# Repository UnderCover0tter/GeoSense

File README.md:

# GeoSense
This repository is the hub for documentation and files created for the project dubbed "GeoSence". 

The goal of this project is to make a circuit to allow for more accurate measuring of a thermistor.
To do achieve this goal a instrumentation amplifier circuit has ben designed for the respective thermistor and operating range of the application.

A later goal is to write a program that will interpret the circuits output from an A to D to get and log the temperatures measured.

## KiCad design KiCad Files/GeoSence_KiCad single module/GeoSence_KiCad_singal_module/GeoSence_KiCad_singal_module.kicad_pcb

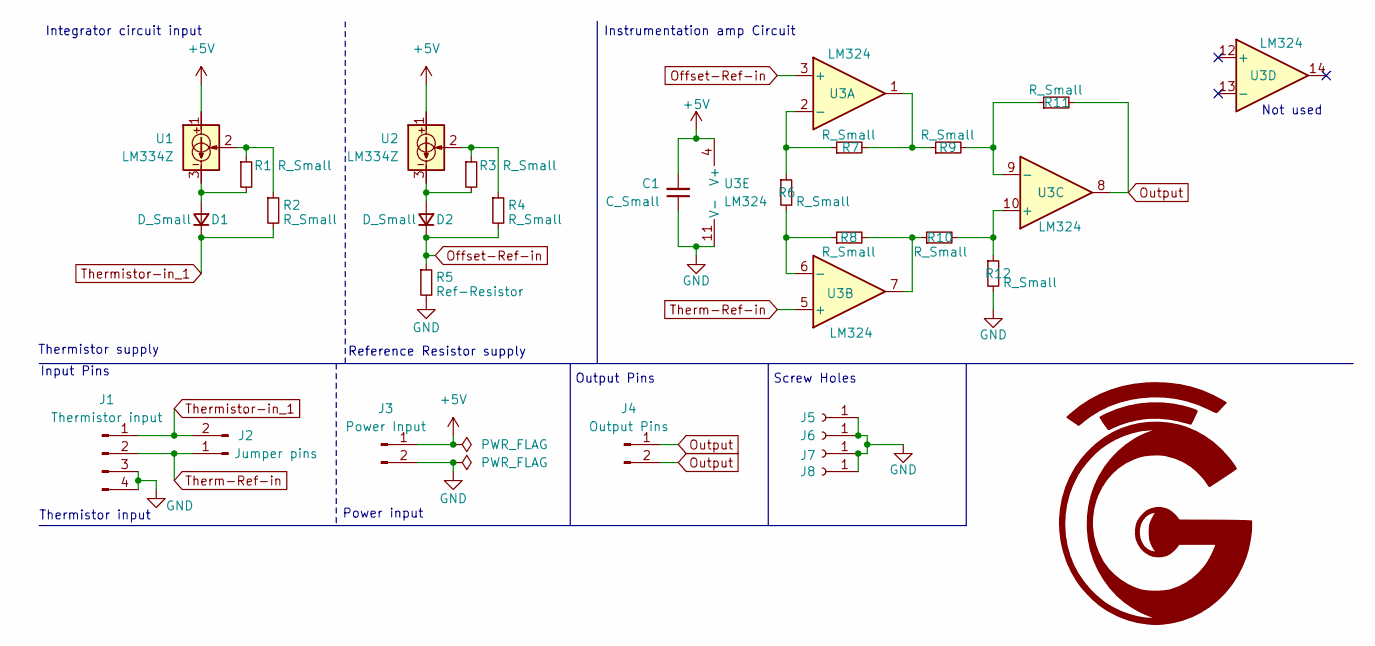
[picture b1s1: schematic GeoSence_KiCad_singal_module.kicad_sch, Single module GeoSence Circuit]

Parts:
C1: C_Small; C_0805_2012Metric
D1, D2: D_Small; D_DO-35_SOD27_P7.62mm_Horizontal
J1: Thermistor input; PinHeader_1x04_P2.54mm_Vertical
J2: Jumper pins; PinHeader_1x02_P2.54mm_Vertical
J3: Power Input; PinHeader_1x02_P2.54mm_Vertical
J4: Output Pins; PinHeader_1x02_P2.54mm_Vertical
J5, J6, J7, J8: Conn_01x01_Socket; MountingHole_3.2mm_M3_DIN965_Pad_TopBottom
R1, R2, R3, R4, R6, R7, R8, R9, R10, R11, R12: R_Small; R_Axial_DIN0204_L3.6mm_D1.6mm_P5.08mm_Horizontal
R5: Ref-Resistor; R_Axial_DIN0204_L3.6mm_D1.6mm_P5.08mm_Horizontal
U1, U2: LM334Z; TO-92_Inline
U3: LM324; TSSOP-14_4.4x5mm_P0.65mm

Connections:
+5V: C1.2, J3.1, U1.1, U2.1, U3.4 (V+)
GND: C1.1, J1.3, J1.4, J3.2, J5.1, J6.1, J7.1, J8.1, R5.2, R12.2, U3.11 (V-)
unnamed: D1.2 (A), R1.2, U1.3
unnamed: D2.2 (A), R3.2, U2.3
unnamed: R1.1, R2.1, U1.2
unnamed: R3.1, R4.1, U2.2
unnamed: R7.2, R9.1, U3.1
unnamed: R8.2, R10.1, U3.7
unnamed: R6.1, R7.1, U3.2 (-)
unnamed: R6.2, R8.1, U3.6 (-)
unnamed: R10.2, R12.1, U3.10 (+)
unnamed: R9.2, R11.1, U3.9 (-)
Offset-Ref-in: D2.1 (K), R4.2, R5.1, U3.3 (+)
Output: J4.1, J4.2, R11.2, U3.8
Therm-Ref-in: J1.2, J2.1, U3.5 (+)
Thermistor-in_1: D1.1 (K), J1.1, J2.2, R2.2

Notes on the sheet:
Reference Resistor supply
Thermistor supply
Thermistor input
Output Pins
Power input
Instrumentation amp Circuit
Not used
Screw Holes
Integrator circuit input
Input Pins

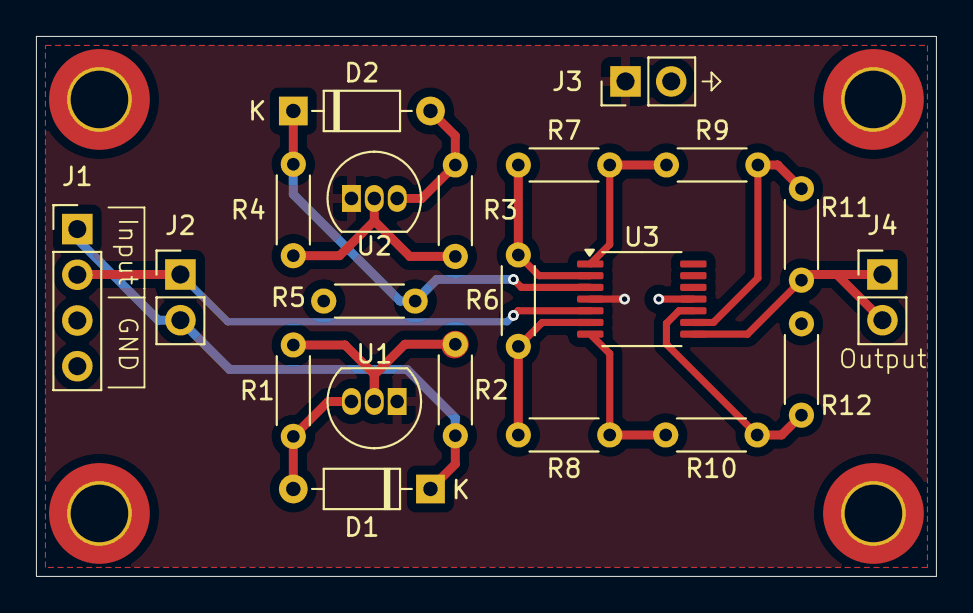
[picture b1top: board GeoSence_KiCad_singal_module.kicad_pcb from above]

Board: 2 copper layers, 50.0 x 30.0 mm, 26 parts (1 on the bottom side), 16 nets.

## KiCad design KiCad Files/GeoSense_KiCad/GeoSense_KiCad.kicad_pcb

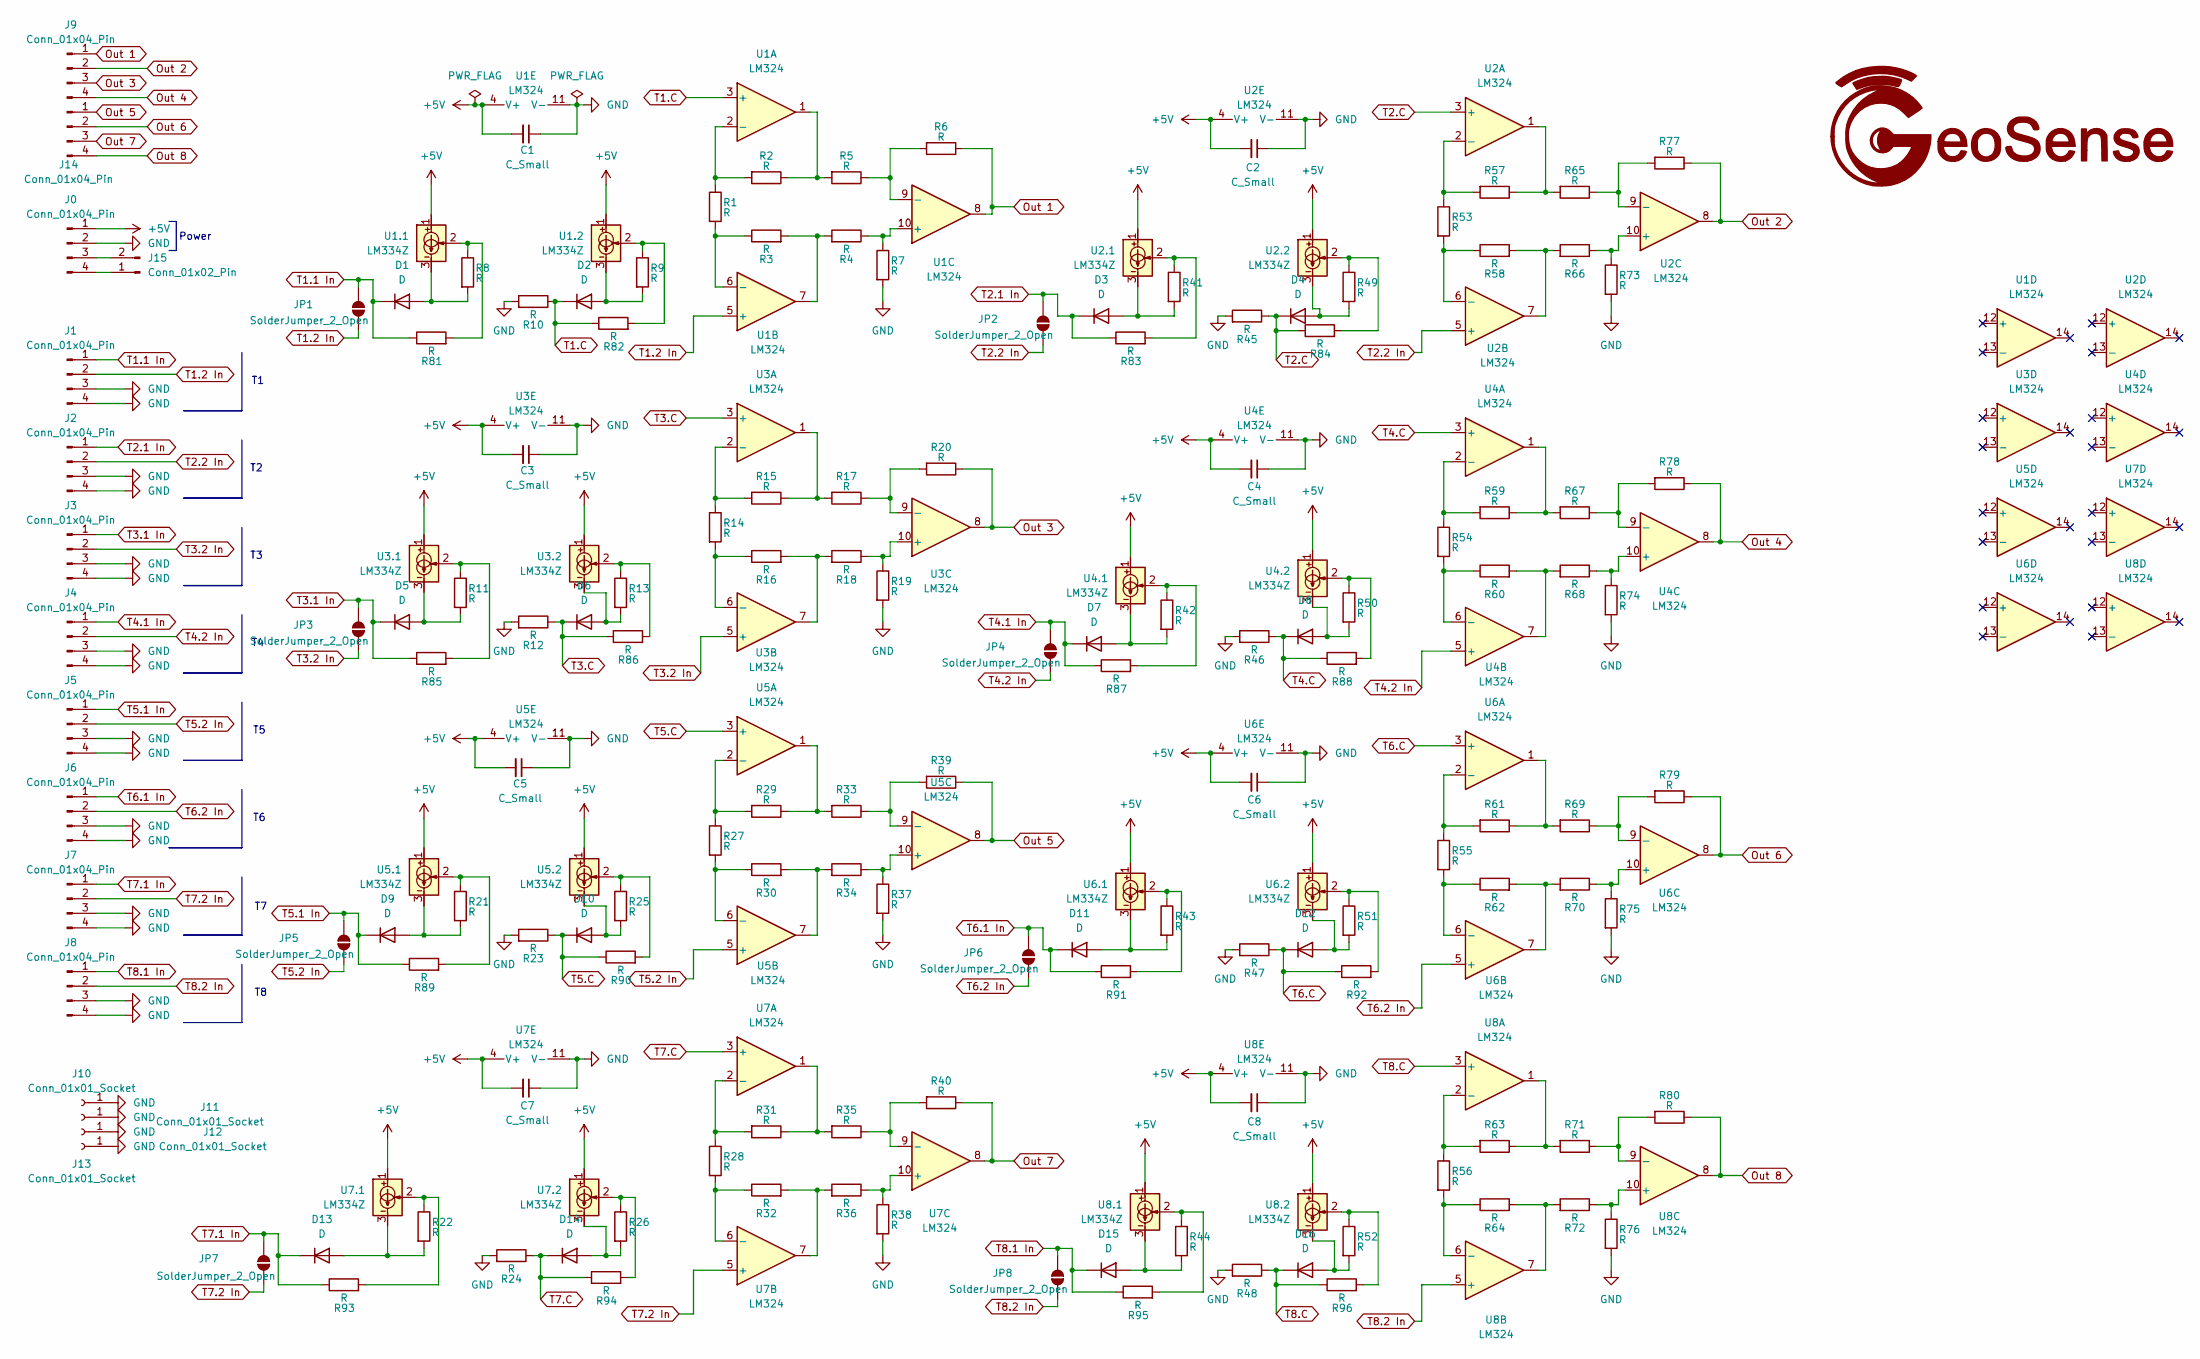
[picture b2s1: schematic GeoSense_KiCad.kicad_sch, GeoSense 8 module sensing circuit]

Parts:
C1, C2, C3, C4, C5, C6, C7, C8: C_Small; C_0603_1608Metric
D1, D2, D3, D4, D5, D6, D7, D8, D9, D10, D11, D12, D13, D14, D15, D16: D; D_DO-35_SOD27_P7.62mm_Horizontal
J0, J1, J2, J3, J4, J5, J6, J7, J8, J9, J14: Conn_01x04_Pin; PinHeader_1x04_P2.54mm_Vertical
J10, J11, J12, J13: Conn_01x01_Socket; MountingHole_3.2mm_M3_DIN965_Pad_TopBottom
J15: Conn_01x02_Pin; PinHeader_1x02_P2.54mm_Vertical
JP1, JP2, JP3, JP4, JP5, JP6, JP7, JP8: SolderJumper_2_Open; SolderJumper-2_P1.3mm_Open_RoundedPad1.0x1.5mm
R1, R2, R3, R4, R5, R6, R7, R8, R9, R10, R11, R12, R13, R14, R15, R16, R17, R18, R19, R20, R21, R22, R23, R24, R25, R26, R27, R28, R29, R30, R31, R32, R33, R34, R35, R36, R37, R38, R39, R40, R41, R42, R43, R44, R45, R46, R47, R48, R49, R50, R51, R52, R53, R54, R55, R56, R57, R58, R59, R60, R61, R62, R63, R64, R65, R66, R67, R68, R69, R70, R71, R72, R73, R74, R75, R76, R77, R78, R79, R80, R81, R82, R83, R84, R85, R86, R87, R88, R89, R90, R91, R92, R93, R94, R95, R96: R; R_Axial_DIN0204_L3.6mm_D1.6mm_P5.08mm_Horizontal
U1, U2, U3, U4, U5, U6, U7, U8: LM324; TSSOP-14_4.4x5mm_P0.65mm
U1.1, U1.2, U2.1, U2.2, U3.1, U3.2, U4.1, U4.2, U5.1, U5.2, U6.1, U6.2, U7.1, U7.2, U8.1, U8.2: LM334Z; TO-92_Inline

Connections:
+5V: C1.2, C2.2, C3.2, C4.2, C5.2, C6.2, C7.2, C8.2, J0.1, U1.4 (V+), U1.1.1, U1.2.1, U2.4 (V+), U2.1.1, U2.2.1, U3.4 (V+), U3.1.1, U3.2.1, U4.4 (V+), U4.1.1, U4.2.1, U5.4 (V+), U5.1.1, U5.2.1, U6.4 (V+), U6.1.1, U6.2.1, U7.4 (V+), U7.1.1, U7.2.1, U8.4 (V+), U8.1.1, U8.2.1
GND: C1.1, C2.1, C3.1, C4.1, C5.1, C6.1, C7.1, C8.1, J0.2, J1.3, J1.4, J2.3, J2.4, J3.3, J3.4, J4.3, J4.4, J5.3, J5.4, J6.3, J6.4, J7.3, J7.4, J8.3, J8.4, J10.1, J11.1, J12.1, J13.1, R7.2, R10.2, R12.2, R19.2, R23.2, R24.2, R37.2, R38.2, R45.2, R46.2, R47.2, R48.2, R73.2, R74.2, R75.2, R76.2, U1.11 (V-), U2.11 (V-), U3.11 (V-), U4.11 (V-), U5.11 (V-), U6.11 (V-), U7.11 (V-), U8.11 (V-)
unnamed: D1.2 (A), R8.2, U1.1.3
unnamed: D2.2 (A), R9.2, U1.2.3
unnamed: D3.2 (A), R41.2, U2.1.3
unnamed: D4.2 (A), R49.2, U2.2.3
unnamed: D5.2 (A), R11.2, U3.1.3
unnamed: D6.2 (A), R13.2, U3.2.3
unnamed: D7.2 (A), R42.2, U4.1.3
unnamed: D8.2 (A), R50.2, U4.2.3
unnamed: D9.2 (A), R21.2, U5.1.3
unnamed: D10.2 (A), R25.2, U5.2.3
unnamed: D11.2 (A), R43.2, U6.1.3
unnamed: D12.2 (A), R51.2, U6.2.3
unnamed: D13.2 (A), R22.2, U7.1.3
unnamed: D14.2 (A), R26.2, U7.2.3
unnamed: D15.2 (A), R44.2, U8.1.3
unnamed: D16.2 (A), R52.2, U8.2.3
unnamed: J0.3, J15.2
unnamed: J0.4, J15.1
unnamed: R2.1, R5.2, U1.1
unnamed: R3.2, R4.2, U1.7
unnamed: R8.1, R81.2, U1.1.2
unnamed: R11.1, R85.2, U3.1.2
unnamed: R13.1, R86.2, U3.2.2
unnamed: R15.1, R17.2, U3.1
unnamed: R16.2, R18.2, U3.7
unnamed: R21.1, R89.2, U5.1.2
unnamed: R22.1, R93.2, U7.1.2
unnamed: R25.1, R90.2, U5.2.2
unnamed: R26.1, R94.2, U7.2.2
unnamed: R29.1, R33.2, U5.1
unnamed: R30.2, R34.2, U5.7
unnamed: R31.1, R35.2, U7.1
unnamed: R32.2, R36.2, U7.7
unnamed: R41.1, R83.2, U2.1.2
unnamed: R42.1, R87.2, U4.1.2
unnamed: R43.1, R91.2, U6.1.2
unnamed: R44.1, R95.2, U8.1.2
unnamed: R49.1, R84.2, U2.2.2
unnamed: R50.1, R88.2, U4.2.2
unnamed: R51.1, R92.2, U6.2.2
unnamed: R52.1, R96.2, U8.2.2
unnamed: R57.1, R65.2, U2.1
unnamed: R58.2, R66.2, U2.7
unnamed: R59.1, R67.2, U4.1
unnamed: R60.2, R68.2, U4.7
unnamed: R61.1, R69.2, U6.1
unnamed: R62.2, R70.2, U6.7
unnamed: R63.1, R71.2, U8.1
unnamed: R64.2, R72.2, U8.7
unnamed: R9.1, R82.2, U1.2.2
unnamed: R1.1, R2.2, U1.2 (-)
unnamed: R1.2, R3.1, U1.6 (-)
unnamed: R4.1, R7.1, U1.10 (+)
unnamed: R5.1, R6.2, U1.9 (-)
unnamed: R53.1, R57.2, U2.2 (-)
unnamed: R53.2, R58.1, U2.6 (-)
unnamed: R66.1, R73.1, U2.10 (+)
unnamed: R65.1, R77.2, U2.9 (-)
unnamed: R14.1, R15.2, U3.2 (-)
unnamed: R14.2, R16.1, U3.6 (-)
unnamed: R18.1, R19.1, U3.10 (+)
unnamed: R17.1, R20.2, U3.9 (-)
unnamed: R54.1, R59.2, U4.2 (-)
unnamed: R54.2, R60.1, U4.6 (-)
unnamed: R68.1, R74.1, U4.10 (+)
unnamed: R67.1, R78.2, U4.9 (-)
unnamed: R27.1, R29.2, U5.2 (-)
unnamed: R27.2, R30.1, U5.6 (-)
unnamed: R34.1, R37.1, U5.10 (+)
unnamed: R33.1, R39.2, U5.9 (-)
unnamed: R55.1, R61.2, U6.2 (-)
unnamed: R55.2, R62.1, U6.6 (-)
unnamed: R70.1, R75.1, U6.10 (+)
unnamed: R69.1, R79.2, U6.9 (-)
unnamed: R28.1, R31.2, U7.2 (-)
unnamed: R28.2, R32.1, U7.6 (-)
unnamed: R36.1, R38.1, U7.10 (+)
unnamed: R35.1, R40.2, U7.9 (-)
unnamed: R56.1, R63.2, U8.2 (-)
unnamed: R56.2, R64.1, U8.6 (-)
unnamed: R72.1, R76.1, U8.10 (+)
unnamed: R71.1, R80.2, U8.9 (-)
Out 1: J9.1, R6.1, U1.8
Out 2: J9.2, R77.1, U2.8
Out 3: J9.3, R20.1, U3.8
Out 4: J9.4, R78.1, U4.8
Out 5: J14.1, R39.1, U5.8
Out 6: J14.2, R79.1, U6.8
Out 7: J14.3, R40.1, U7.8
Out 8: J14.4, R80.1, U8.8
T1.1 In: D1.1 (K), J1.1, JP1.2 (B), R81.1
T1.2 In: J1.2, JP1.1 (A), U1.5 (+)
T1.C: D2.1 (K), R10.1, R82.1, U1.3 (+)
T2.1 In: D3.1 (K), J2.1, JP2.2 (B), R83.1
T2.2 In: J2.2, JP2.1 (A), U2.5 (+)
T2.C: D4.1 (K), R45.1, R84.1, U2.3 (+)
T3.1 In: D5.1 (K), J3.1, JP3.2 (B), R85.1
T3.2 In: J3.2, JP3.1 (A), U3.5 (+)
T3.C: D6.1 (K), R12.1, R86.1, U3.3 (+)
T4.1 In: D7.1 (K), J4.1, JP4.2 (B), R87.1
T4.2 In: J4.2, JP4.1 (A), U4.5 (+)
T4.C: D8.1 (K), R46.1, R88.1, U4.3 (+)
T5.1 In: D9.1 (K), J5.1, JP5.2 (B), R89.1
T5.2 In: J5.2, JP5.1 (A), U5.5 (+)
T5.C: D10.1 (K), R23.1, R90.1, U5.3 (+)
T6.1 In: D11.1 (K), J6.1, JP6.2 (B), R91.1
T6.2 In: J6.2, JP6.1 (A), U6.5 (+)
T6.C: D12.1 (K), R47.1, R92.1, U6.3 (+)
T7.1 In: D13.1 (K), J7.1, JP7.2 (B), R93.1
T7.2 In: J7.2, JP7.1 (A), U7.5 (+)
T7.C: D14.1 (K), R24.1, R94.1, U7.3 (+)
T8.1 In: D15.1 (K), J8.1, JP8.2 (B), R95.1
T8.2 In: J8.2, JP8.1 (A), U8.5 (+)
T8.C: D16.1 (K), R48.1, R96.1, U8.3 (+)

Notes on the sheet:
Power

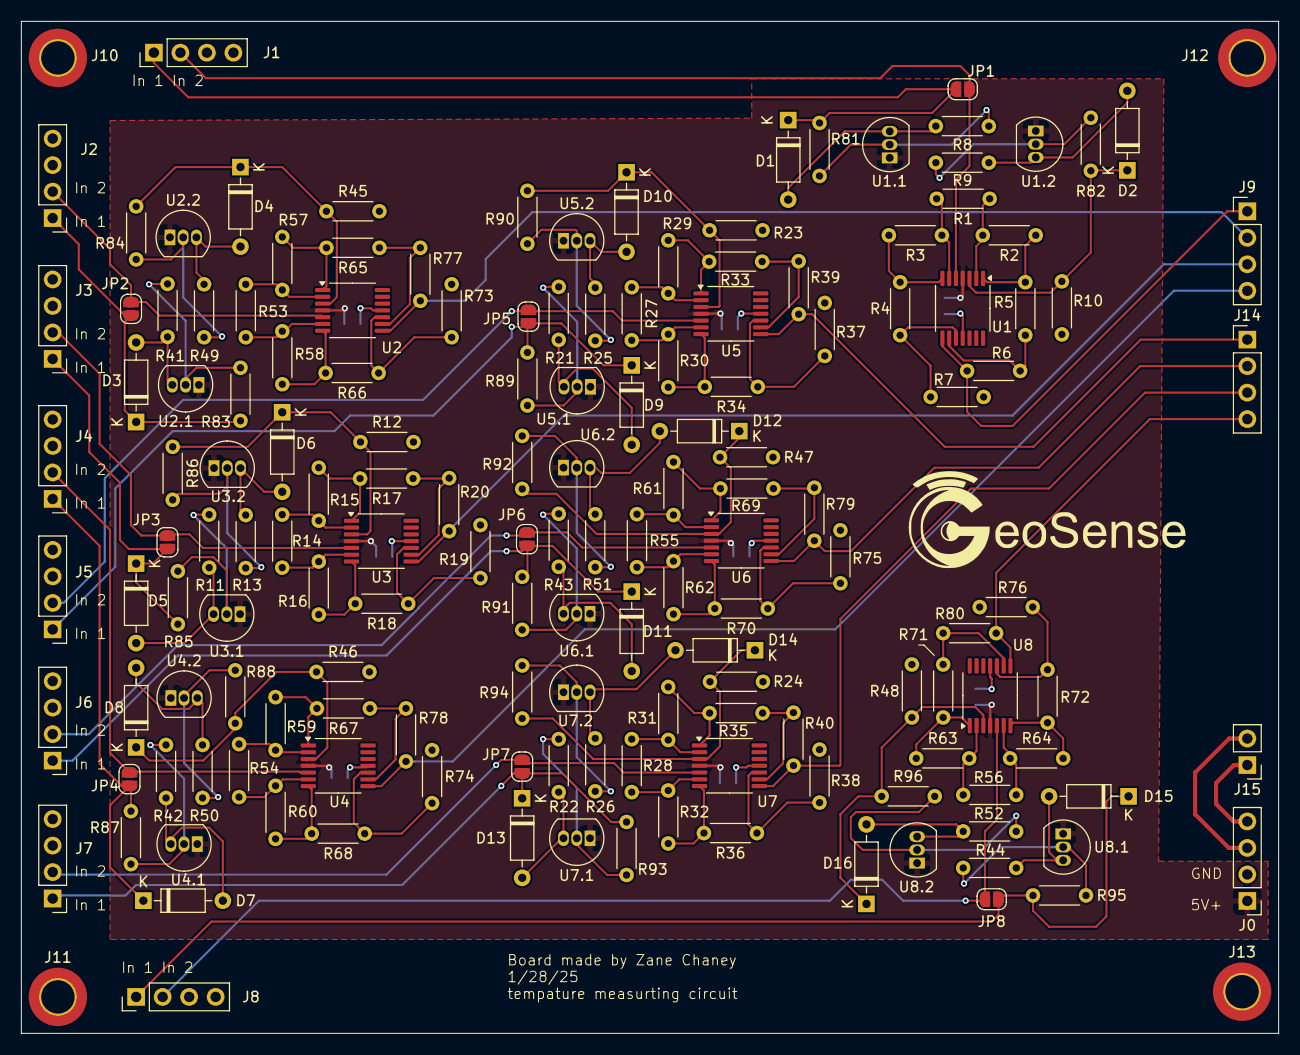
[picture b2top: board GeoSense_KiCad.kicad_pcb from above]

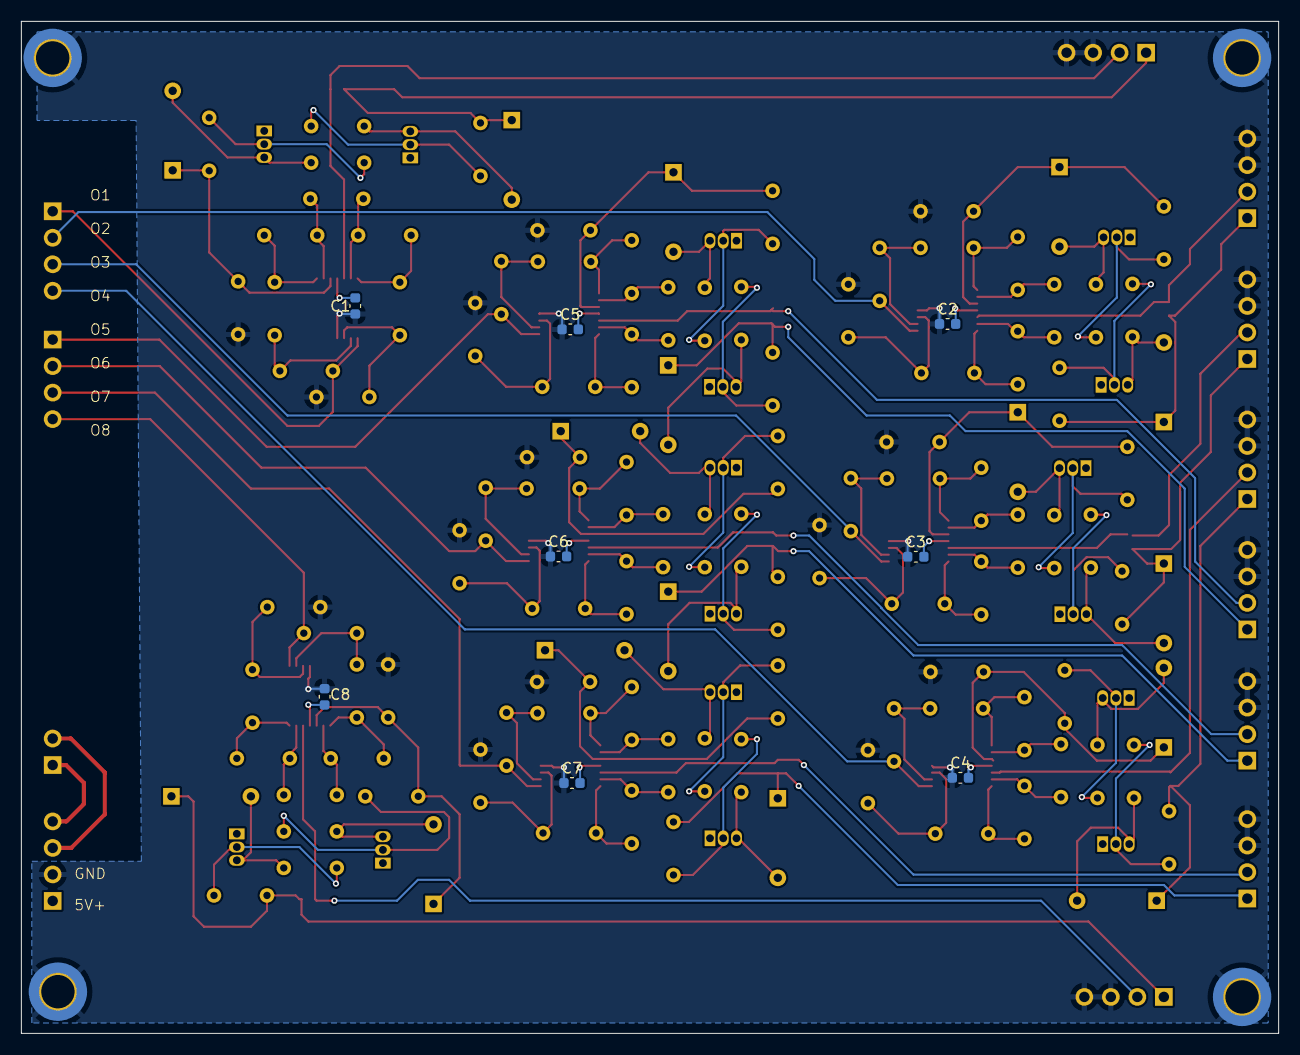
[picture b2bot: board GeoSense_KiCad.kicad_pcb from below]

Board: 2 copper layers, 120.5 x 97.0 mm, 168 parts (8 on the bottom side), 116 nets.

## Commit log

2025-01-04 Added the blank KiCad files
2025-01-04 Added blank footprint and symbol files for use in KiCad
2025-01-05 Added the blank files for the LTspice circuit design
2025-01-05 added the circuit for the 10k configuration
2025-01-05 added the 1k thermistor circuit to LTspice
2025-01-12 Changed the resistor values
    These new values match a more standard resistance value. this will make procurement of parts easier with less conflicts in resistor size.
2025-02-03 added the 8 modules
2025-02-05 added the jumpers
    added the jumper connections to allow for transition between a 4 and 2 wire thermistor.
2025-02-08 2/7/25
2025-02-08 finished the schematic
2025-02-08 made the schematic pdf
2025-02-08 added logo
2025-02-11 fixed wrong 3rd stage opamp wiring
2025-02-11 fixed opamp conections
2025-02-13 updated the schematic
2025-02-15 added the decoupling caps to the ltspice simulation
2025-02-15 added caps
2025-02-17 part way through the pcb design
2025-02-25 pcb mainly built
2025-02-28 added to diodes to the schematic
    need to reroute the pcb
2025-02-28 added diodes and resistors to pcb
    silkscreen needs fixing
2025-02-28 finished the silkscreen edits
2025-03-12 added an invoice file
2025-03-12 edit
2025-04-05 added the single module version
2025-04-05 updated to kicad 9.0.1
2025-04-05 generated gerber files
2025-04-08 added initial design image
